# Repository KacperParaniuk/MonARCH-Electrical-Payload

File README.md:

# MonARCH Payload Interface Board

## Getting started

To make it easy for you to get started with GitLab, here's a list of recommended next steps.

Already a pro? Just edit this README.md and make it your own. Want to make it easy? [Use the template at the bottom](#editing-this-readme)!

## Add your files

- [ ] [Create](https://docs.gitlab.com/ee/user/project/repository/web_editor.html#create-a-file) or [upload](https://docs.gitlab.com/ee/user/project/repository/web_editor.html#upload-a-file) files
- [ ] [Add files using the command line](https://docs.gitlab.com/topics/git/add_files/#add-files-to-a-git-repository) or push an existing Git repository with the following command:

```
cd existing_repo
git remote add origin https://gitlab.engr.illinois.edu/cubesat/monarch-payload-interface-board.git
git branch -M main
git push -uf origin main
```

## Integrate with your tools

- [ ] [Set up project integrations](https://gitlab.engr.illinois.edu/cubesat/monarch-payload-interface-board/-/settings/integrations)

## Collaborate with your team

- [ ] [Invite team members and collaborators](https://docs.gitlab.com/ee/user/project/members/)
- [ ] [Create a new merge request](https://docs.gitlab.com/ee/user/project/merge_requests/creating_merge_requests.html)
- [ ] [Automatically close issues from merge requests](https://docs.gitlab.com/ee/user/project/issues/managing_issues.html#closing-issues-automatically)
- [ ] [Enable merge request approvals](https://docs.gitlab.com/ee/user/project/merge_requests/approvals/)
- [ ] [Set auto-merge](https://docs.gitlab.com/user/project/merge_requests/auto_merge/)

## Test and Deploy

Use the built-in continuous integration in GitLab.

- [ ] [Get started with GitLab CI/CD](https://docs.gitlab.com/ee/ci/quick_start/)
- [ ] [Analyze your code for known vulnerabilities with Static Application Security Testing (SAST)](https://docs.gitlab.com/ee/user/application_security/sast/)
- [ ] [Deploy to Kubernetes, Amazon EC2, or Amazon ECS using Auto Deploy](https://docs.gitlab.com/ee/topics/autodevops/requirements.html)
- [ ] [Use pull-based deployments for improved Kubernetes management](https://docs.gitlab.com/ee/user/clusters/agent/)
- [ ] [Set up protected environments](https://docs.gitlab.com/ee/ci/environments/protected_environments.html)

***

# Editing this README

When you're ready to make this README your own, just edit this file and use the handy template below (or feel free to structure it however you want - this is just a starting point!). Thanks to [makeareadme.com](https://www.makeareadme.com/) for this template.

## Suggestions for a good README

Every project is different, so consider which of these sections apply to yours. The sections used in the template are suggestions for most open source projects. Also keep in mind that while a README can be too long and detailed, too long is better than too short. If you think your README is too long, consider utilizing another form of documentation rather than cutting out information.

## Name
Choose a self-explaining name for your project.

## Description
Let people know what your project can do specifically. Provide context and add a link to any reference visitors might be unfamiliar with. A list of Features or a Background subsection can also be added here. If there are alternatives to your project, this is a good place to list differentiating factors.

## Badges
On some READMEs, you may see small images that convey metadata, such as whether or not all the tests are passing for the project. You can use Shields to add some to your README. Many services also have instructions for adding a badge.

## Visuals
Depending on what you are making, it can be a good idea to include screenshots or even a video (you'll frequently see GIFs rather than actual videos). Tools like ttygif can help, but check out Asciinema for a more sophisticated method.

## Installation
Within a particular ecosystem, there may be a common way of installing things, such as using Yarn, NuGet, or Homebrew. However, consider the possibility that whoever is reading your README is a novice and would like more guidance. Listing specific steps helps remove ambiguity and gets people to using your project as quickly as possible. If it only runs in a specific context like a particular programming language version or operating system or has dependencies that have to be installed manually, also add a Requirements subsection.

## Usage
Use examples liberally, and show the expected output if you can. It's helpful to have inline the smallest example of usage that you can demonstrate, while providing links to more sophisticated examples if they are too long to reasonably include in the README.

## Support
Tell people where they can go to for help. It can be any combination of an issue tracker, a chat room, an email address, etc.

## Roadmap
If you have ideas for releases in the future, it is a good idea to list them in the README.

## Contributing
State if you are open to contributions and what your requirements are for accepting them.

For people who want to make changes to your project, it's helpful to have some documentation on how to get started. Perhaps there is a script that they should run or some environment variables that they need to set. Make these steps explicit. These instructions could also be useful to your future self.

You can also document commands to lint the code or run tests. These steps help to ensure high code quality and reduce the likelihood that the changes inadvertently break something. Having instructions for running tests is especially helpful if it requires external setup, such as starting a Selenium server for testing in a browser.

## Authors and acknowledgment
Show your appreciation to those who have contributed to the project.

## License
For open source projects, say how it is licensed.

## Project status
If you have run out of energy or time for your project, put a note at the top of the README saying that development has slowed down or stopped completely. Someone may choose to fork your project or volunteer to step in as a maintainer or owner, allowing your project to keep going. You can also make an explicit request for maintainers.

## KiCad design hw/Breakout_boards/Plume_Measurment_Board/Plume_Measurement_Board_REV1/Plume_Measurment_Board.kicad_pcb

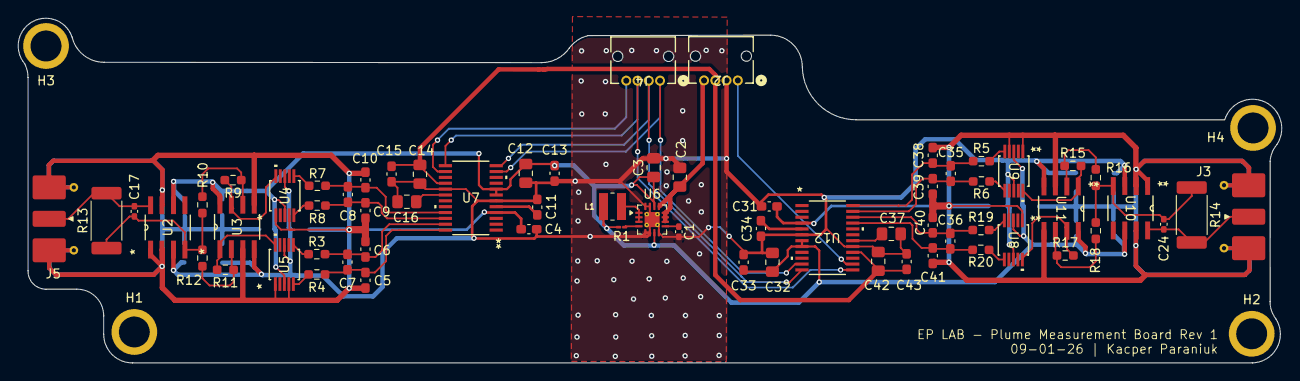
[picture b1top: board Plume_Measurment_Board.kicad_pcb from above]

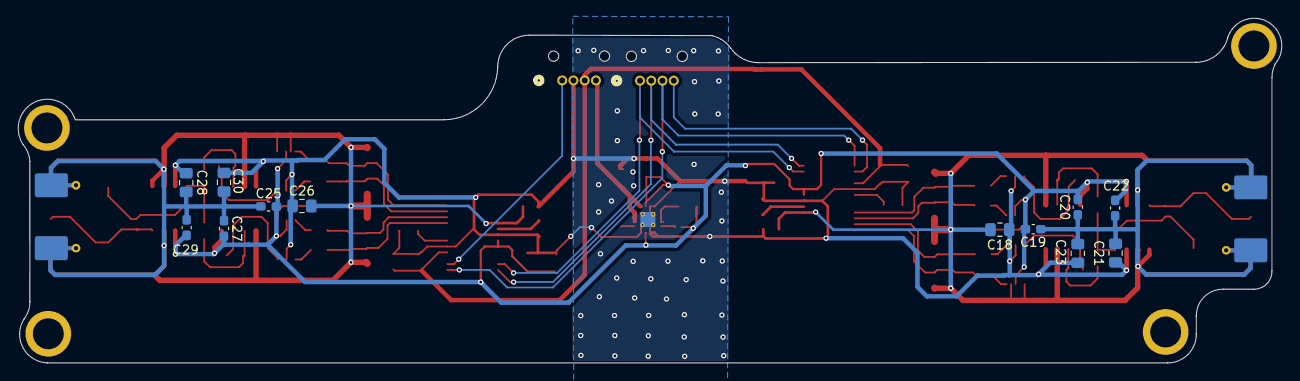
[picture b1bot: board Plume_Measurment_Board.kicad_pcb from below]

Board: 2 copper layers, 140.3 x 38.3 mm, 82 parts (12 on the bottom side), 46 nets.

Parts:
C1: 620pF; C_0402_1005Metric_Pad0.74x0.62mm_HandSolder
C2, C12, C14, C32, C42: 10uF; C_0805_2012Metric_Pad1.18x1.45mm_HandSolder
C3: 22uF; C_0805_2012Metric_Pad1.18x1.45mm_HandSolder
C4, C31: .1uF; C_0603_1608Metric_Pad1.08x0.95mm_HandSolder
C5, C6, C9, C10, C38, C39, C40, C41: 270pF; C_0603_1608Metric_Pad1.08x0.95mm_HandSolder
C7, C8, C35, C36: 680pF; C_0603_1608Metric_Pad1.08x0.95mm_HandSolder
C11, C19, C20, C22, C25, C27, C29, C34: 1uF; C_0603_1608Metric_Pad1.08x0.95mm_HandSolder
C13, C15, C33, C43: 100nF; C_0603_1608Metric_Pad1.08x0.95mm_HandSolder
C16, C18, C21, C23, C26, C28, C30, C37: 1uF; C_0805_2012Metric_Pad1.18x1.45mm_HandSolder
C17, C24: .1pF; C_0402_1005Metric_Pad0.74x0.62mm_HandSolder
H1, H2, H3, H4: MountingHole; MountingHole_2.5mm
J2, J4: Conn_01x04; Molex_Micro-Lock_2200980471_1x04_P1.25mm_Horizontal
J3, J5: Conn_Coaxial; SMA_Molex_73251-2120_EdgeMount_Horizontal
L1: 2.2uH; IND_VLS3012CX-2R2M-1
R1: 100k; R_01005_0402Metric_Pad0.57x0.30mm_HandSolder
R3, R4, R5, R6, R7, R8, R19, R20: 10; R_0603_1608Metric_Pad0.98x0.95mm_HandSolder
R9, R10, R11, R12, R15, R16, R17, R18: 1000; R_0603_1608Metric_Pad0.98x0.95mm_HandSolder
R13, R14: 1G; R_2512_6332Metric_Pad1.40x3.35mm_HandSolder
U2, U10: LMP7721MA/NOPB; M08A
U3, U11: LMP2022MA/NOPB; M08A
U4, U5, U8, U9: AD8475ARMZ; RM_10_ADI
U6: TPS62153; VQFN-16-1EP_3x3mm_P0.5mm_EP1.68x1.68mm_ThermalVias
U7, U12: AD7176-2BRUZ; RU_24_ADI

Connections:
+3V3: C14.2, C15.2, C42.2, C43.2, J2.3, U7.16 (IOVDD), U12.16 (IOVDD)
+5V: C3.1, C12.2, C13.2, C19.2, C20.2, C22.2, C25.2, C27.2, C29.2, C32.2, C33.2, L1.2, R1.2, U2.6 (V+), U3.8 (V+), U4.3 (VS+), U5.3 (VS+), U6.7 (FSW), U6.14 (VOS), U7.7 (AVDD1), U7.8 (AVDD2), U8.3 (VS+), U9.3 (VS+), U10.6 (V+), U11.8 (V+), U12.7 (AVDD1), U12.8 (AVDD2)
/+VBAT: C2.1, J2.4, U6.10 (VIN), U6.11 (VIN), U6.12 (VIN), U6.13 (EN)
/E-Spray Plume Measurement 1/1_IN0.8+: R9.2, U3.7 (OUTB), U4.10 (IN0.8X+)
/E-Spray Plume Measurement 1/2_IN0.8+: R11.2, U3.1 (OUTA), U5.10 (IN0.8X+)
/E-Spray Plume Measurement 1/+2.5V: C4.1, C5.2, C6.1, C9.2, C10.1, C18.2, C19.1, C20.1, C21.2, C22.1, C23.2, J5.2 (Ext), U2.1 (IN+), U2.2 (NC), U2.7 (NC), U3.3 (INA+), U3.5 (INB+), U4.1 (IN0.8X-), U4.4 (VOCM), U5.1 (IN0.8X-), U5.4 (VOCM), U7.4 (REFOUT)
/E-Spray Plume Measurement 1/+OUT_1: R8.2, U4.5 (OUT+)
/E-Spray Plume Measurement 1/+OUT_2: R4.2, U5.5 (OUT+)
/E-Spray Plume Measurement 1/-OUT_1: R7.2, U4.6 (OUT-)
/E-Spray Plume Measurement 1/-OUT_2: R3.2, U5.6 (OUT-)
/E-Spray Plume Measurement 1/Amplified_Plume_1: C17.2, R10.1, R12.1, R13.1, U2.4 (OUT)
/E-Spray Plume Measurement 1/Plume_1: C17.1, J5.1 (In), R13.2, U2.8 (IN-)
/E-Spray Plume Measurement 2/3_IN0.8+: R17.2, U8.10 (IN0.8X+), U11.7 (OUTB)
/E-Spray Plume Measurement 2/4_IN0.8+: R15.2, U9.10 (IN0.8X+), U11.1 (OUTA)
/E-Spray Plume Measurement 2/+2.5V: C25.1, C26.2, C27.1, C28.2, C29.1, C30.2, C31.1, C38.2, C39.1, C40.2, C41.1, J3.2 (Ext), U8.1 (IN0.8X-), U8.4 (VOCM), U9.1 (IN0.8X-), U9.4 (VOCM), U10.1 (IN+), U10.2 (NC), U10.7 (NC), U11.3 (INA+), U11.5 (INB+), U12.4 (REFOUT)
/E-Spray Plume Measurement 2/+OUT_3: R19.2, U8.5 (OUT+)
/E-Spray Plume Measurement 2/+OUT_4: R5.2, U9.5 (OUT+)
/E-Spray Plume Measurement 2/-OUT_3: R20.2, U8.6 (OUT-)
/E-Spray Plume Measurement 2/-OUT_4: R6.2, U9.6 (OUT-)
/E-Spray Plume Measurement 2/Amplified_Plume_2: C24.2, R14.1, R16.1, R18.1, U10.4 (OUT)
/E-Spray Plume Measurement 2/Plume_2: C24.1, J3.1 (In), R14.2, U10.8 (IN-)
/PM_CS_1: J4.4, U7.14 (*CS)
/PM_CS_2: J2.1, U12.14 (*CS)
/SPI1_MISO: J4.1, U7.11 (DOUT/*RDY), U12.11 (DOUT/*RDY)
/SPI1_MOSI: J4.2, U7.12 (DIN), U12.12 (DIN)
/SPI1_SCK: J4.3, U7.13 (SCLK), U12.13 (SCLK)
GND: C1.2, C2.2, C3.2, C4.2, C11.2, C12.1, C13.1, C14.1, C15.1, C16.1, C18.1, C21.1, C23.1, C26.1, C28.1, C30.1, C31.2, C32.1, C33.1, C34.2, C37.1, C42.1, C43.1, J2.2, U2.3 (V-), U3.4 (V-), U4.8 (VS-), U5.8 (VS-), U6.5 (FB), U6.6 (GND), U6.8 (DEF), U6.15 (GND), U6.16 (GND), U6.17 (GND), U7.6 (AVSS), U7.17 (DGND), U8.8 (VS-), U9.8 (VS-), U10.3 (V-), U11.4 (V-), U12.6 (AVSS), U12.17 (DGND)
unnamed: L1.1, U6.1 (SW), U6.2 (SW), U6.3 (SW)
unnamed: R11.1, R12.2, U3.2 (INA-)
unnamed: R9.1, R10.2, U3.6 (INB-)
unnamed: R1.1, U6.4 (PG)
unnamed: C1.1, U6.9 (SS/TR)
unnamed: C8.2, C10.2, R7.1, U7.21 (AIN0)
unnamed: C8.1, C9.1, R8.1, U7.22 (AIN1)
unnamed: C6.2, C7.2, R3.1, U7.23 (AIN2)
unnamed: C5.1, C7.1, R4.1, U7.24 (AIN3)
unnamed: C11.1, U7.5 (REGCAPA)
unnamed: C16.2, U7.18 (REGCAPD)
unnamed: R15.1, R16.2, U11.2 (INA-)
unnamed: R17.1, R18.2, U11.6 (INB-)
unnamed: C36.2, C41.2, R20.1, U12.21 (AIN0)
unnamed: C36.1, C40.1, R19.1, U12.22 (AIN1)
unnamed: C35.2, C39.2, R6.1, U12.23 (AIN2)
unnamed: C35.1, C38.1, R5.1, U12.24 (AIN3)
unnamed: C34.1, U12.5 (REGCAPA)
unnamed: C37.2, U12.18 (REGCAPD)

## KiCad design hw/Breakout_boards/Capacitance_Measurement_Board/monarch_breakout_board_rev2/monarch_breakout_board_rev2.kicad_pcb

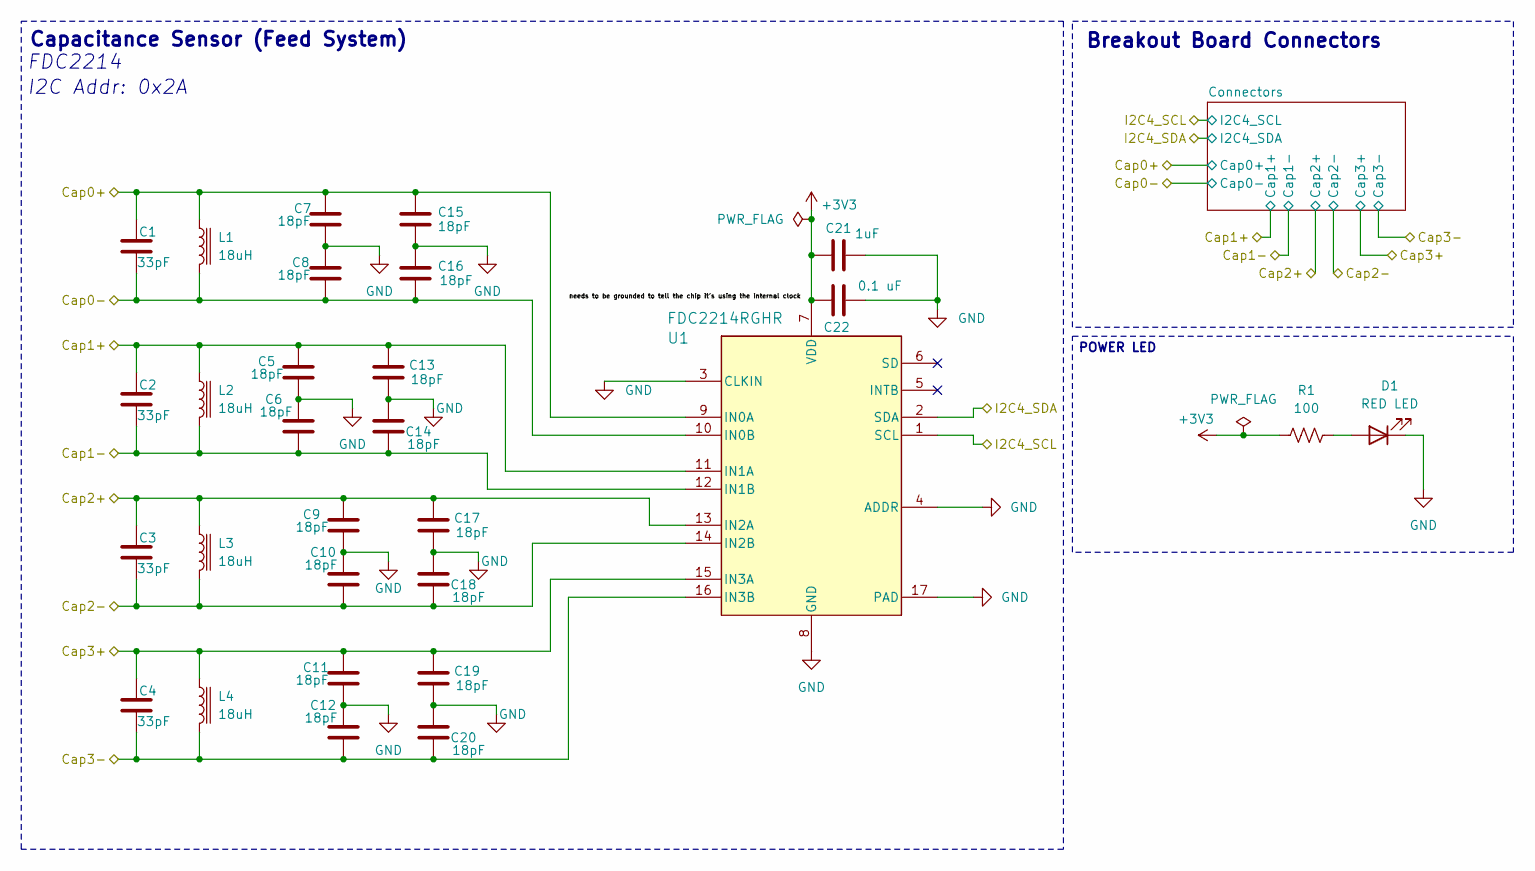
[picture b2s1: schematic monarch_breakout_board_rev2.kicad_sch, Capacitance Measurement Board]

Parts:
C1, C2, C3, C4: 33pF; C_0603_1608Metric
C5, C6, C7, C8, C9, C10, C11, C12, C13, C14, C15, C16, C17, C18, C19, C20: 18pF; C_0603_1608Metric
C21: 1uF; C_0603_1608Metric
C22: 0.1 uF; C_0603_1608Metric
D1: RED LED; LED_0603_1608Metric_Pad1.05x0.95mm_HandSolder
L1, L2, L3, L4: 18uH; INDM3225X240N
R1: 100; R_0603_1608Metric_Pad0.98x0.95mm_HandSolder
U1: FDC2214RGHR; RGH0016A

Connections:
+3V3: C21.2, C22.2, R1.1, U1.7 (VDD); also elsewhere on the board
/Cap0+: C1.1, C7.1, C15.1, L1.1, U1.9 (IN0A); also elsewhere on the board
/Cap0-: C1.2, C8.2, C16.2, L1.2, U1.10 (IN0B); also elsewhere on the board
/Cap1+: C2.1, C5.1, C13.1, L2.1, U1.11 (IN1A); also elsewhere on the board
/Cap1-: C2.2, C6.2, C14.2, L2.2, U1.12 (IN1B); also elsewhere on the board
/Cap2+: C3.1, C9.1, C17.1, L3.1, U1.13 (IN2A); also elsewhere on the board
/Cap2-: C3.2, C10.2, C18.2, L3.2, U1.14 (IN2B); also elsewhere on the board
/Cap3+: C4.1, C11.1, C19.1, L4.1, U1.15 (IN3A); also elsewhere on the board
/Cap3-: C4.2, C12.2, C20.2, L4.2, U1.16 (IN3B); also elsewhere on the board
/I2C4_SCL: U1.1 (SCL); also elsewhere on the board
/I2C4_SDA: U1.2 (SDA); also elsewhere on the board
GND: C5.2, C6.1, C7.2, C8.1, C9.2, C10.1, C11.2, C12.1, C13.2, C14.1, C15.2, C16.1, C17.2, C18.1, C19.2, C20.1, C21.1, C22.1, D1.1 (K), U1.3 (CLKIN), U1.4 (ADDR), U1.8 (GND), U1.17 (PAD), U1.V; also elsewhere on the board
unnamed: D1.2 (A), R1.2

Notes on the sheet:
POWER LED
I2C Addr: 0x2A
Breakout Board Connectors
FDC2214
Capacitance Sensor (Feed System)

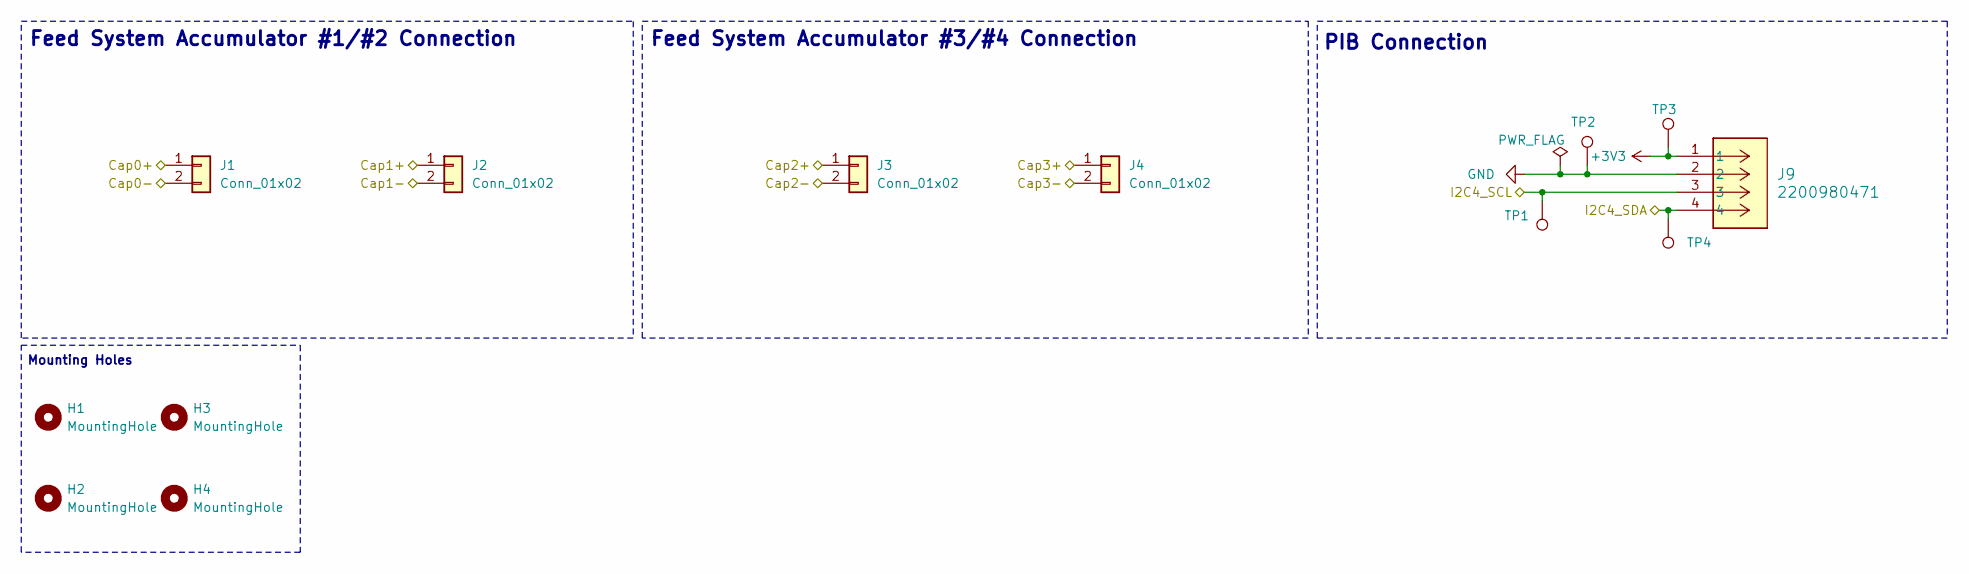
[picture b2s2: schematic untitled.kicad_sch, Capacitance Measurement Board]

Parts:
H1, H2, H3, H4: MountingHole; MountingHole_2.2mm_M2_DIN965_Pad
J1, J2, J3, J4: Conn_01x02; Molex_Micro-Lock_2200980271_1x02_P1.25mm_Horizontal
J9: 2200980471; Molex_Micro-Lock_2200980471_1x04_P1.25mm_Horizontal
TP1, TP2, TP3, TP4: TestPoint; TestPoint_Keystone_5000-5004_Miniature

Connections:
+3V3: J9.1, TP3.1; also elsewhere on the board
/Cap0+: J1.1; also elsewhere on the board
/Cap0-: J1.2; also elsewhere on the board
/Cap1+: J2.1; also elsewhere on the board
/Cap1-: J2.2; also elsewhere on the board
/Cap2+: J3.1; also elsewhere on the board
/Cap2-: J3.2; also elsewhere on the board
/Cap3+: J4.1; also elsewhere on the board
/Cap3-: J4.2; also elsewhere on the board
/I2C4_SCL: J9.3, TP1.1; also elsewhere on the board
/I2C4_SDA: J9.4, TP4.1; also elsewhere on the board
GND: J9.2, TP2.1; also elsewhere on the board

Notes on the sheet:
Mounting Holes
PIB Connection
Feed System Accumulator #1/#2 Connection
Feed System Accumulator #3/#4 Connection

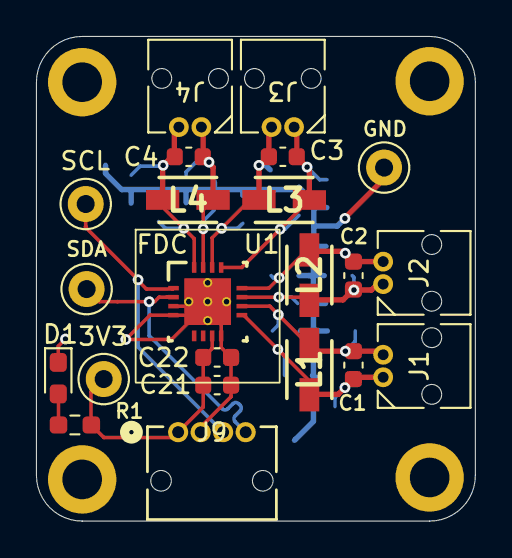
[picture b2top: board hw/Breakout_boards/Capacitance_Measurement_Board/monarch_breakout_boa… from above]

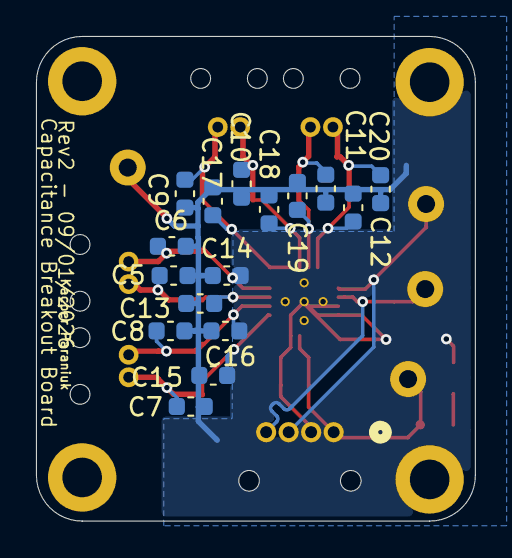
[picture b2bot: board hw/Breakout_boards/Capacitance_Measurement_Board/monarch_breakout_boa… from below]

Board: 2 copper layers, 24.4 x 26.9 mm, 42 parts (16 on the bottom side), 13 nets.

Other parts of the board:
3V3: TestPoint; TestPoint_Keystone_5000-5004_Miniature
GND: TestPoint; TestPoint_Keystone_5000-5004_Miniature
SCL: TestPoint; TestPoint_Keystone_5000-5004_Miniature
SDA: TestPoint; TestPoint_Keystone_5000-5004_Miniature

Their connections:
+3V3: 3V3.1 (1_1); also elsewhere on the board
/I2C4_SCL: SCL.1 (1_1); also elsewhere on the board
/I2C4_SDA: SDA.1 (1_1); also elsewhere on the board
GND: GND.1 (1_1); also elsewhere on the board

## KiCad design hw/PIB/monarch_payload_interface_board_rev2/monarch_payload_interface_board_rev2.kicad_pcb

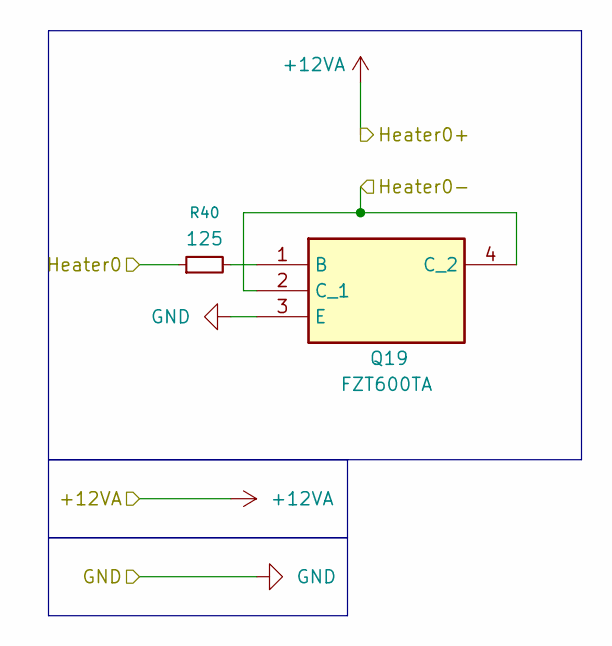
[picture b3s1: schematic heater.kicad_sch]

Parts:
Q19: FZT600TA; SOT230P700X170-4N; Mouser Part Number 522-FZT600TA
R40: 125; R_0603_1608Metric

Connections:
12VA_VA-: Q19.3 (E); also elsewhere on the board
/Connectors/Heater0-: Q19.2 (C_1), Q19.4 (C_2); also elsewhere on the board
/Heater/Heater0: R40.1; also elsewhere on the board
unnamed: Q19.1 (B), R40.2

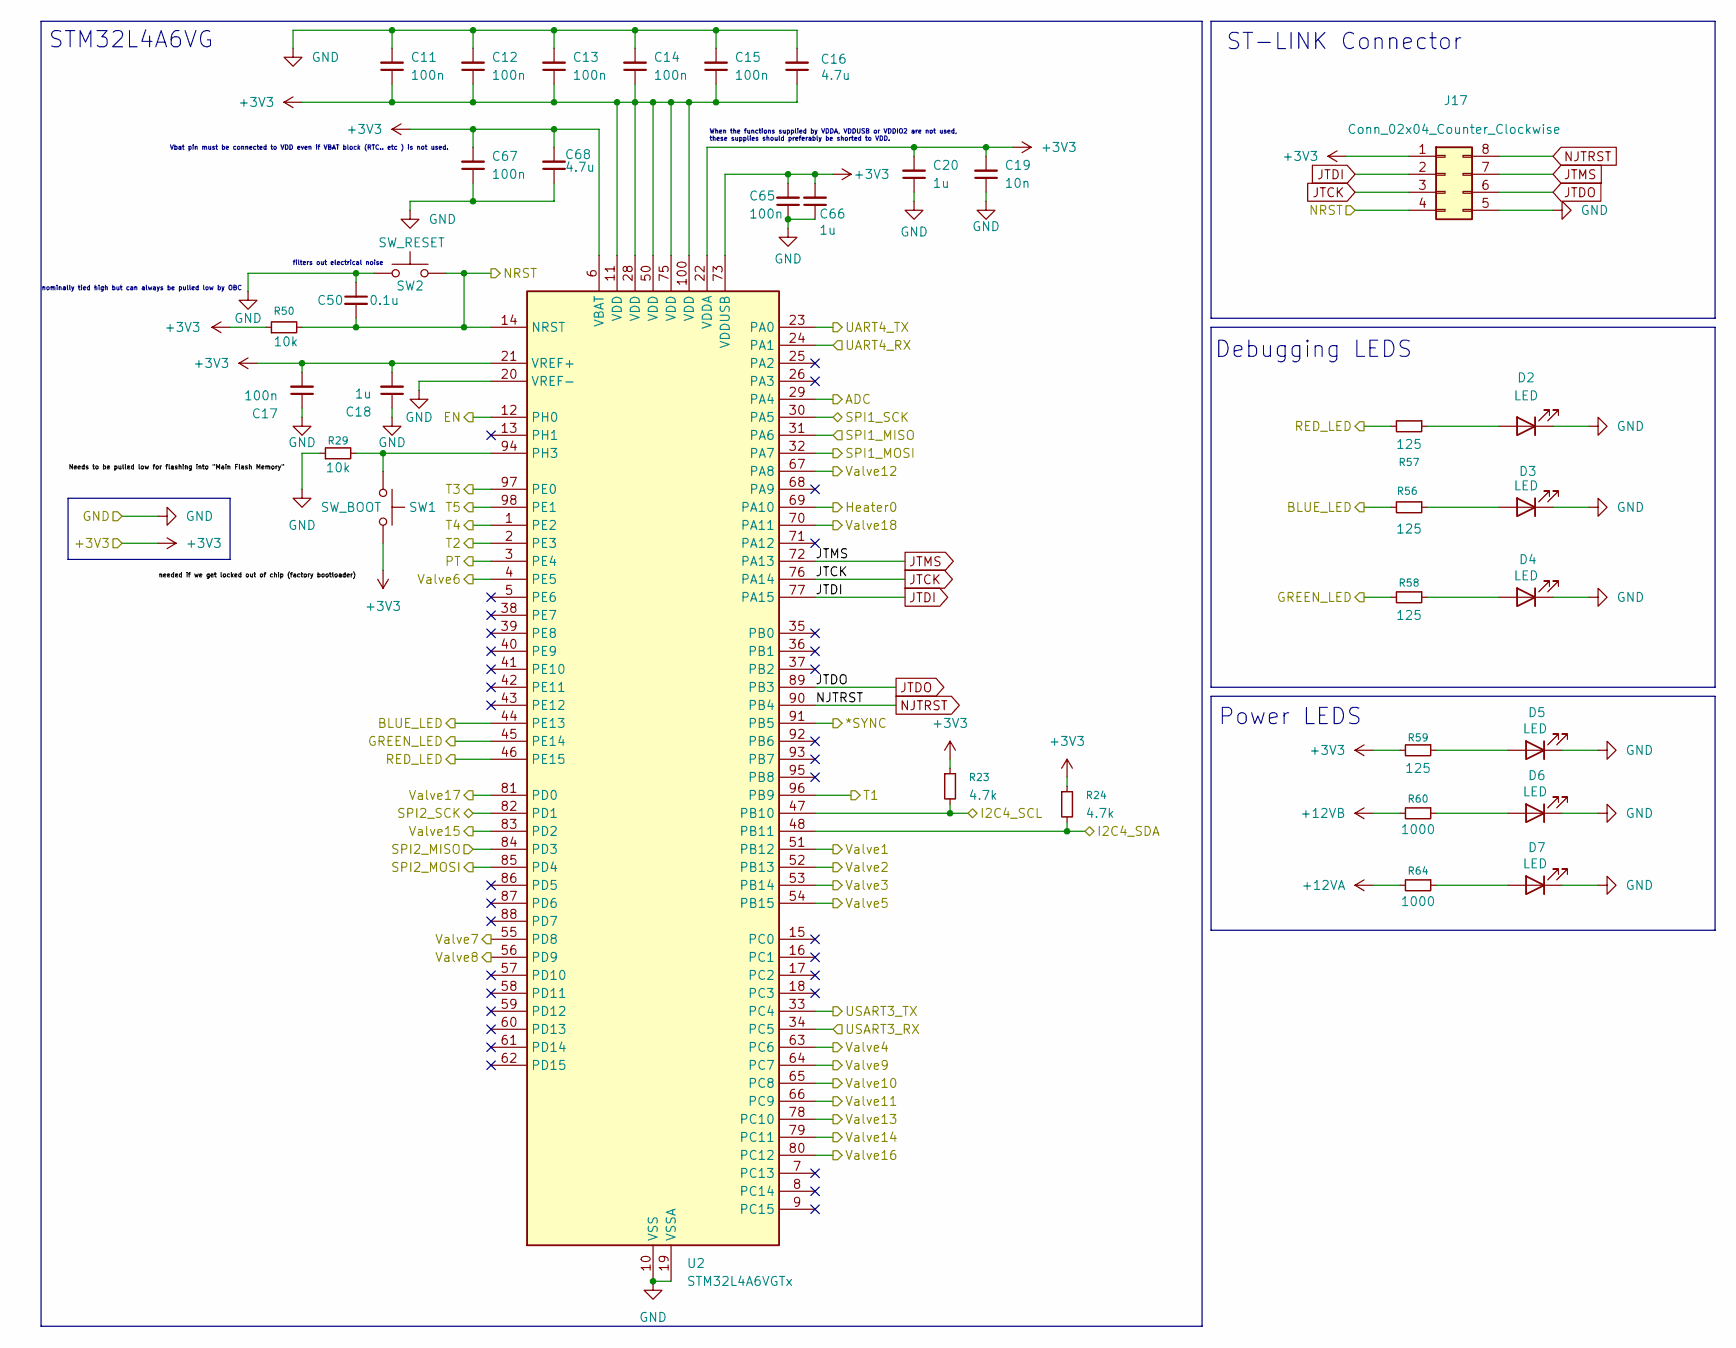
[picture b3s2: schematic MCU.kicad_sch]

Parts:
C11, C12, C13, C14, C15, C17, C65, C67: 100n; C_0603_1608Metric
C16, C68: 4.7u; C_0603_1608Metric
C18, C20, C66: 1u; C_0603_1608Metric
C19: 10n; C_0603_1608Metric
C50: 0.1u; C_0603_1608Metric
D2, D3, D4, D5, D6, D7: LED; LED_0603_1608Metric
J17: Conn_02x04_Counter_Clockwise; PinHeader_2x04_P2.54mm_Vertical
R23, R24: 4.7k; R_0603_1608Metric
R29, R50: 10k; R_0603_1608Metric
R56, R57, R58, R59: 125; R_0603_1608Metric
R60, R64: 1000; R_0603_1608Metric
SW1: SW_BOOT; PinHeader_1x02_P1.00mm_Vertical
SW2: SW_RESET; PinHeader_1x02_P1.00mm_Vertical
U2: STM32L4A6VGTx; LQFP-100_14x14mm_P0.5mm

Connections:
12VA_VA-: C11.2, C12.2, C13.2, C14.2, C15.2, C16.2, C17.1, C18.1, C19.1, C20.1, C50.1, C65.1, C66.1, C67.1, C68.1, D2.1 (K), D3.1 (K), D4.1 (K), D5.1 (K), D6.1 (K), D7.1 (K), J17.5, R29.1, SW2.1, U2.10 (VSS), U2.19 (VSSA), U2.20 (VREF-), U2.27 (VSS), U2.49 (VSS), U2.74 (VSS), U2.99 (VSS); also elsewhere on the board
+3V3: C11.1, C12.1, C13.1, C14.1, C15.1, C16.1, C17.2, C18.2, C19.2, C20.2, C65.2, C66.2, C67.2, C68.2, J17.1, R23.1, R24.1, R50.1, R59.2, SW1.2, U2.6 (VBAT), U2.11 (VDD), U2.21 (VREF+), U2.22 (VDDA), U2.28 (VDD), U2.50 (VDD), U2.73 (VDDUSB), U2.75 (VDD), U2.100 (VDD); also elsewhere on the board
+12VA: R64.2; also elsewhere on the board
+12VB: R60.2; also elsewhere on the board
/12V Power Supply/EN: U2.12 (PH0); also elsewhere on the board
/Connectors/*SYNC: U2.91 (PB5); also elsewhere on the board
/Connectors/ADC: U2.29 (PA4); also elsewhere on the board
/Connectors/I2C4_SCL: R23.2, U2.47 (PB10); also elsewhere on the board
/Connectors/I2C4_SDA: R24.2, U2.48 (PB11); also elsewhere on the board
/Connectors/PT: U2.3 (PE4); also elsewhere on the board
/Connectors/SPI1_MISO: U2.31 (PA6); also elsewhere on the board
/Connectors/SPI1_MOSI: U2.32 (PA7); also elsewhere on the board
/Connectors/SPI1_SCK: U2.30 (PA5); also elsewhere on the board
/Connectors/SPI2_MISO: U2.84 (PD3); also elsewhere on the board
/Connectors/SPI2_MOSI: U2.85 (PD4); also elsewhere on the board
/Connectors/SPI2_SCK: U2.82 (PD1); also elsewhere on the board
/Connectors/T1: U2.96 (PB9); also elsewhere on the board
/Connectors/T2: U2.2 (PE3); also elsewhere on the board
/Connectors/T3: U2.97 (PE0); also elsewhere on the board
/Connectors/T4: U2.1 (PE2); also elsewhere on the board
/Connectors/T5: U2.98 (PE1); also elsewhere on the board
/Connectors/UART_PPU_RX: U2.23 (PA0); also elsewhere on the board
/Connectors/UART_PPU_TX: U2.24 (PA1); also elsewhere on the board
/Connectors/USART3_RX: U2.34 (PC5); also elsewhere on the board
/Connectors/USART3_TX: U2.33 (PC4); also elsewhere on the board
/Heater/Heater0: U2.69 (PA10); also elsewhere on the board
/MCU/BLUE_LED: R56.2, U2.44 (PE13)
/MCU/GREEN_LED: R58.2, U2.45 (PE14)
/MCU/NRST: C50.2, J17.4, R50.2, SW2.2, U2.14 (NRST); also elsewhere on the board
/MCU/RED_LED: R57.2, U2.46 (PE15)
/MCU/Valve1: U2.51 (PB12); also elsewhere on the board
/MCU/Valve2: U2.52 (PB13); also elsewhere on the board
/MCU/Valve3: U2.53 (PB14); also elsewhere on the board
/MCU/Valve4: U2.63 (PC6); also elsewhere on the board
/MCU/Valve5: U2.54 (PB15); also elsewhere on the board
/MCU/Valve6: U2.4 (PE5); also elsewhere on the board
/MCU/Valve7: U2.55 (PD8); also elsewhere on the board
/MCU/Valve8: U2.56 (PD9); also elsewhere on the board
/MCU/Valve9: U2.64 (PC7); also elsewhere on the board
/MCU/Valve10: U2.65 (PC8); also elsewhere on the board
/MCU/Valve11: U2.66 (PC9); also elsewhere on the board
/MCU/Valve12: U2.67 (PA8); also elsewhere on the board
/MCU/Valve13: U2.78 (PC10); also elsewhere on the board
/MCU/Valve14: U2.79 (PC11); also elsewhere on the board
/MCU/Valve15: U2.83 (PD2); also elsewhere on the board
/MCU/Valve16: U2.80 (PC12); also elsewhere on the board
/MCU/Valve17: U2.81 (PD0); also elsewhere on the board
/MCU/Valve18: U2.70 (PA11); also elsewhere on the board
JTCK: J17.3, U2.76 (PA14)
JTDI: J17.2, U2.77 (PA15)
JTDO: J17.6, U2.89 (PB3)
JTMS: J17.7, U2.72 (PA13)
NJTRST: J17.8, U2.90 (PB4)
unnamed: D2.2 (A), R57.1
unnamed: D3.2 (A), R56.1
unnamed: D4.2 (A), R58.1
unnamed: D5.2 (A), R59.1
unnamed: D6.2 (A), R60.1
unnamed: D7.2 (A), R64.1
unnamed: R29.2, SW1.1, U2.94 (PH3)

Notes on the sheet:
nominally tied high but can always be pulled low by OBC
Debugging LEDS
filters out electrical noise
Power LEDS
When the functions supplied by VDDA, VDDUSB or VDDIO2 are not used, these supplies should preferably be shorted to VDD.
ST-LINK Connector
Vbat pin must be connected to VDD even if VBAT block (RTC.. etc ) is not used.
STM32L4A6VG

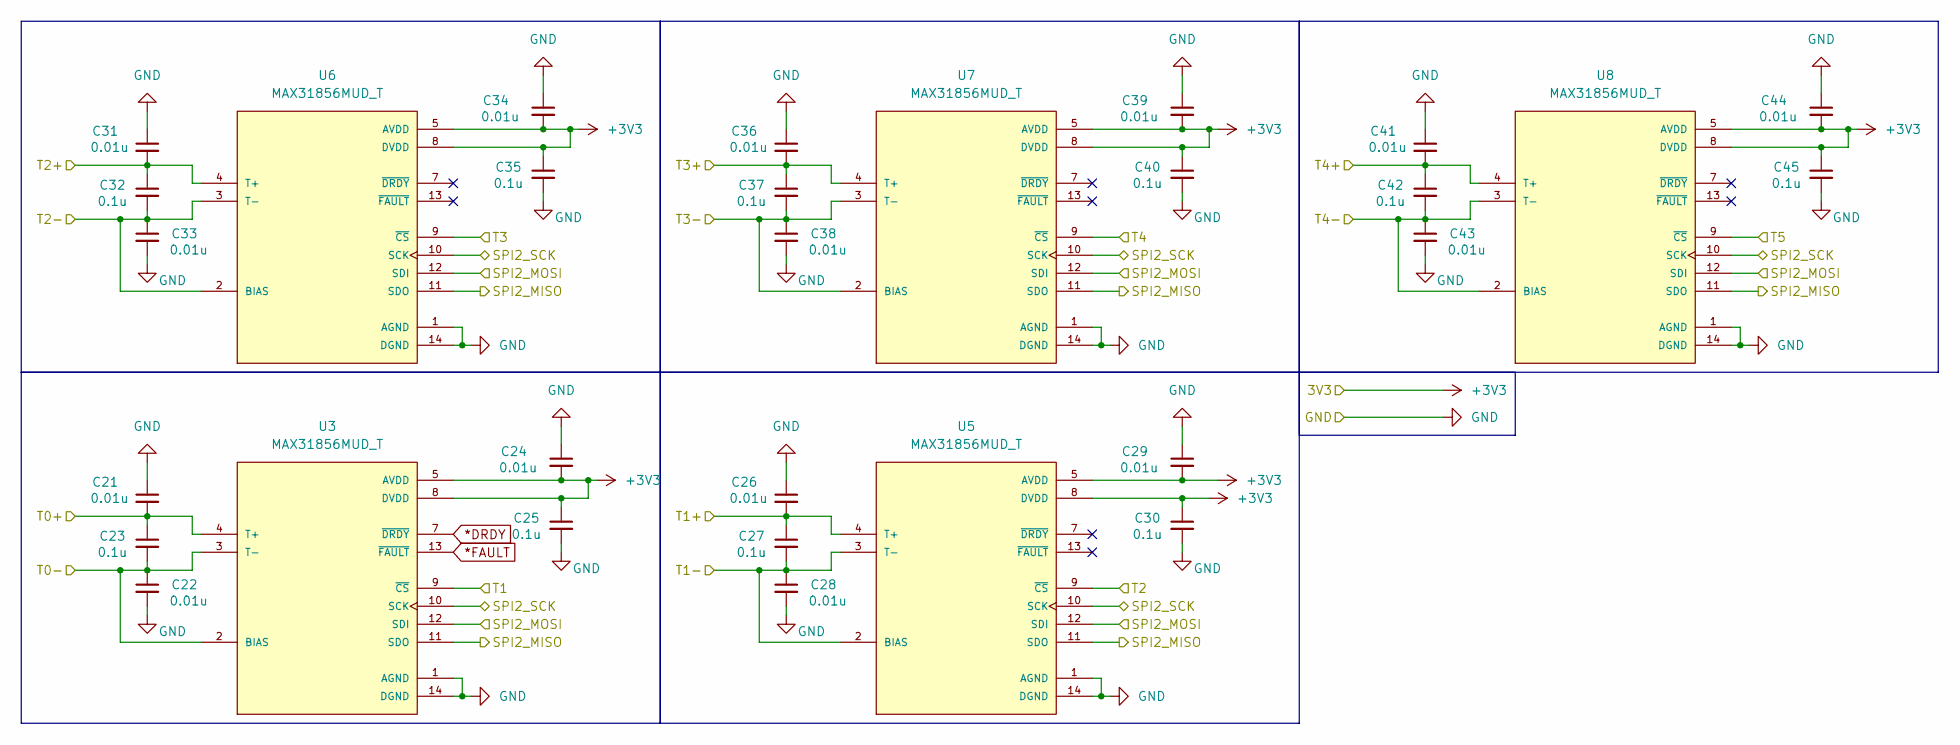
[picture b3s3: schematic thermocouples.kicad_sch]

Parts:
C21, C22, C24, C26, C28, C29, C31, C33, C34, C36, C38, C39, C41, C43, C44: 0.01u; C_0603_1608Metric
C23, C25, C27, C30, C32, C35, C37, C40, C42, C45: 0.1u; C_0603_1608Metric
U3, U5, U6, U7, U8: MAX31856MUD_T; SOP65P640X110-14N; PARTREV 0

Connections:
12VA_VA-: C21.1, C22.2, C24.1, C25.2, C26.1, C28.2, C29.1, C30.2, C31.1, C33.2, C34.1, C35.2, C36.1, C38.2, C39.1, C40.2, C41.1, C43.2, C44.1, C45.2, U3.1 (AGND), U3.14 (DGND), U5.1 (AGND), U5.14 (DGND), U6.1 (AGND), U6.14 (DGND), U7.1 (AGND), U7.14 (DGND), U8.1 (AGND), U8.14 (DGND); also elsewhere on the board
*DRDY: U3.7 (~DRDY); also elsewhere on the board
*FAULT: U3.13 (~FAULT); also elsewhere on the board
+3V3: C24.2, C25.1, C29.2, C30.1, C34.2, C35.1, C39.2, C40.1, C44.2, C45.1, U3.5 (AVDD), U3.8 (DVDD), U5.5 (AVDD), U5.8 (DVDD), U6.5 (AVDD), U6.8 (DVDD), U7.5 (AVDD), U7.8 (DVDD), U8.5 (AVDD), U8.8 (DVDD); also elsewhere on the board
/Connectors/SPI2_MISO: U3.11 (SDO), U5.11 (SDO), U6.11 (SDO), U7.11 (SDO), U8.11 (SDO); also elsewhere on the board
/Connectors/SPI2_MOSI: U3.12 (SDI), U5.12 (SDI), U6.12 (SDI), U7.12 (SDI), U8.12 (SDI); also elsewhere on the board
/Connectors/SPI2_SCK: U3.10 (SCK), U5.10 (SCK), U6.10 (SCK), U7.10 (SCK), U8.10 (SCK); also elsewhere on the board
/Connectors/T0+: C21.2, C23.1, U3.4 (T+); also elsewhere on the board
/Connectors/T0-: C22.1, C23.2, U3.2 (BIAS), U3.3 (T-); also elsewhere on the board
/Connectors/T1: U3.9 (~CS); also elsewhere on the board
/Connectors/T1+: C26.2, C27.1, U5.4 (T+); also elsewhere on the board
/Connectors/T1-: C27.2, C28.1, U5.2 (BIAS), U5.3 (T-); also elsewhere on the board
/Connectors/T2: U5.9 (~CS); also elsewhere on the board
/Connectors/T2+: C31.2, C32.1, U6.4 (T+); also elsewhere on the board
/Connectors/T2-: C32.2, C33.1, U6.2 (BIAS), U6.3 (T-); also elsewhere on the board
/Connectors/T3: U6.9 (~CS); also elsewhere on the board
/Connectors/T3+: C36.2, C37.1, U7.4 (T+); also elsewhere on the board
/Connectors/T3-: C37.2, C38.1, U7.2 (BIAS), U7.3 (T-); also elsewhere on the board
/Connectors/T4: U7.9 (~CS); also elsewhere on the board
/Connectors/T4+: C41.2, C42.1, U8.4 (T+); also elsewhere on the board
/Connectors/T4-: C42.2, C43.1, U8.2 (BIAS), U8.3 (T-); also elsewhere on the board
/Connectors/T5: U8.9 (~CS); also elsewhere on the board
